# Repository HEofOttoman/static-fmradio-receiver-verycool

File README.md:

# static-fmradio-receiver
~~I have given up on unique hardware project names~~

A simple & 'compact' FM receiver

### Schematic

### Case
I tried getting a wood looking material but I don't know how to do that. [Onshape link](https://cad.onshape.com/documents/d116dc6652ebf1960d912e23/w/4509aea471f96bc38b5cdf53/e/2a97019c88efc150ac7c4dbc)

## BOM
Things in the kit (for my own reference)
- 1 x Seeed Studio Xiao RP2040
- 2 x RDA5807 Module
- 2 x 10K WH148 Dual Gang Potentiometer
- 2 x 12mm Momentary Push Button
- 2 x Audio Jack
- 2 x TDA2822 Amplifiers
- 1 x 3.5mm Antenna
- 10 x 5mm LEDs
- 10 x M2.5 Screws
- 10 x M2.5 Heat Inserts, OD 3.5mm
- 10 x 100uF Capacitors
- 10 x 10K Resistors

|Qty|Name|
|---|---|
|john|hard|

## Inspirations
"Diy radio kit"

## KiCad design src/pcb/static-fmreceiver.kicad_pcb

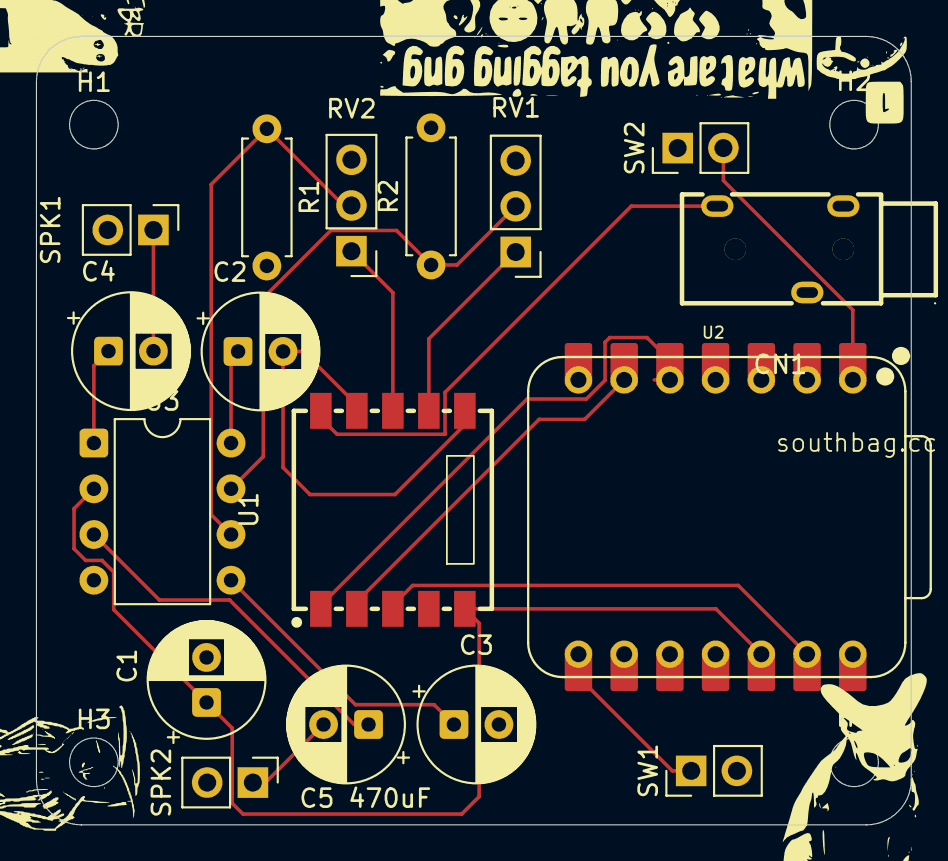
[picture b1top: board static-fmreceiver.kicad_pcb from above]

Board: 2 copper layers, 48.6 x 43.8 mm, 21 parts (0 on the bottom side), 17 nets.

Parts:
C1, C2, C3: 100uF; CP_Radial_D6.3mm_P2.50mm
C4, C5 470uF: 470uF; CP_Radial_D6.3mm_P2.50mm
CN1: PJ-3200; AUDIO-TH_PJ-3200
H1, H2, H3, H4: MountingHole; MountingHole_2.7mm_M2.5
R1, R2: 10K; R_Axial_DIN0207_L6.3mm_D2.5mm_P7.62mm_Horizontal
RV1, RV2: R_Potentiometer 10K; PinHeader_1x03_P2.54mm_Vertical
SPK1: Conn_01x02 (SPKR_R); PinHeader_1x02_P2.54mm_Vertical
SPK2: Conn_01x02 (SPKR_L); PinHeader_1x02_P2.54mm_Vertical
SW1, SW2: SW_Push; PinHeader_1x02_P2.54mm_Vertical
U1: RDA5807MRRD-102V2.0; RDA5807
U2: XIAO-RP2040-DIP
U3: TDA2822NBD; DIP-8_W7.62mm

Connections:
+3V3: C1.1, U1.5 (VCC), U2.12 (3V3), U3.2 (VCC)
/L_AMP_OUT: C5 470uF.2, SPK2.1
/L_OUT: RV1.1, U1.7 (L-OUT)
/R_AMP_OUT: C4.2, SPK1.1
/R_OUT: RV2.1, U1.8 (R-OUT)
/SCL: U1.2 (CLK), U2.6 (P7_SCL_D5)
/SDA: U1.1 (DATA), U2.5 (P6_SDA_D4)
GND: C1.2, C2.2, C3.2, CN1.3, R1.2, R2.2, RV1.3, RV2.3, SPK1.2, SPK2.2, SW1.2, SW2.1, U1.3 (GND), U1.6 (GND), U1.9 (GND), U2.13 (GND), U3.4 (GND)
unnamed: CN1.4, U1.10 (ANT)
unnamed: SW1.1, U2.8 (P1_D7_RX)
unnamed: SW2.2, U2.1 (P26_A0_D0)
unnamed: R2.1, RV1.2, U3.7 (IN1)
unnamed: R1.1, RV2.2, U3.6 (IN2)
unnamed: C2.1, U3.8 (NF1)
unnamed: C3.1, U3.5 (NF2)
unnamed: C4.1, U3.1 (OUT1)
unnamed: C5 470uF.1, U3.3 (OUT2)
